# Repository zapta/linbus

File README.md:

ARDUINO LINBUS GADGETS
======================

An Arduino based LINBUS stack that allow to explore and hack linbus based system.

Unless specified otherwise, the PCBs can be used with standard Aruduino IDE, behaving as Arduino Pro Mini 5V 16Mhz with ATMEGA328.

<br>
**Analyzer** - a small PCB that connects on one hand to linbus and to a computer USB port on the other. The analyzer decode all the linbus frames and dump them to the computer. The USB connection emulates a serial port using a builtin FTDI adapter and can be read with standard serial application. A special python script is provided in the tools directory to dump the serial data in diff mode such that only changed bits are displayed. The board design support also linbus TX which allow to have this board functioning as a linbus master or slave (this however requires firmware changes).

<br>
**Beeper** - a small PCB and firmware that monitors a linbus and activates a buzzer when certain conditions met. The provided firmware includes a car specific example that beeps when the reverse gear in my car is engaged. The car specific logic is in the car_module* files and can be adapted to different applications.

<br>
**Injector** - a small PCB board with two linbus interfaces that connects in series between a linbus master and a linbus slave. The injector looks as a slave to the master and as a master to slave and it transparantly proxying LIN frame between the. At the same time, it can monitor bus signals, apply application spefici logic and can inject signals back to the bus by modifying on the fly LIN frames it proxys between the master and the slave. The Injector was developed to modiy the behavior of existing LIN bus based system (e.g. automatic activation of the Sport mode in my car).

<br>
**Feature Comparison**

| Feature | Analyzer | Beeper | Injector |
|----|----|----|----|
| Max LIN speed | 20kps | 20kps | 20kps |
| Min LIN speed | 1kps | 1kps | 1kps |
| Operating voltage | 12V | 12V | 12V |
| Max voltage | 40V | 40V | 40V |
| LIN frame dump/log | Yes | Yes | Yes |
| LIN checksums | V1/V2 | V1/V2 | V1/V2 |
| Computer serial interface | FTDI/USB | Serial 5V | Serial 5V |
| Computer serial speed | 115,200 | 115,200 | 115,200 |
| Audible output | No | Yes | No |
| LIN signal interception | Yes | Yes | Yes |
| LIN signal injection | No | No | Yes |
| Arduino IDE compatible | Yes | Yes | Yes |
| Programming language | C/C++ | C/C++ | C/C++ |
| MCU | ATMEGA328P | ATMEGA328P  | ATMEGA328P |
| MCU speed | 16Mhz | 16Mhz  | 16Mhz |
| Schematic/Layout software | Cadsoft Eagle | Cadsoft Eagle | Cadsoft Eagle |
| PCB Size (inches) | 1.3 x 1.5 | 1.15 x 1.6 | 1.31 x 1.44 |
| PCB layers | 2 | 2 | 2 |
| Component mounting | SMD | SMD | SMD |
| Min component size | 0805 | 0805 | 0805 |
| OSHPark compatible | Yes | Yes | Yes |

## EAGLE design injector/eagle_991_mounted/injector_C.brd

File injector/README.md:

Arduino LINBUS Signal Injector
==============================

The Arduino Linbus injector is a small Arduino based board that connects on a LIN bus between the master and a slave
and can observe and manipulate the data flowing on the bus. It also has a 115kbs serial interface  programming and for logging bus activity on a standard computer (a serial to FTDI USB adapter such as Sparkfun FTDI Basic is required).

The board has two LIN bus ports, one that acts as a slave and should be connected to the LIN bus master and another
 that acts as a master and should be connected to the LIN bus slace. The firmware here includes a set of files named
with the prefix custom_ that implement an application specific logic (simulating pressing the Sport Mode button of my
car whenever the ignition is turned) and should be modified to match the target logic and behavior.

The USB/Serial port is also compatible with the Arduino IDE (emulating an Arduino Mini Pro 16Mhz 5V with Atmega328p) which can be used to edit/compile/download software updates. 

The serial output of the injector can be viewed directly with a terminal emulation software or using the provided script that adds timestamp and bit by bit diff capabilities (see the [serial tool](../tools/serial)).

The injector provided sample application is configured for 19,200bps linbus that uses LIN V2 checksum but be configured 
for busses with different speeds and checksum formula.

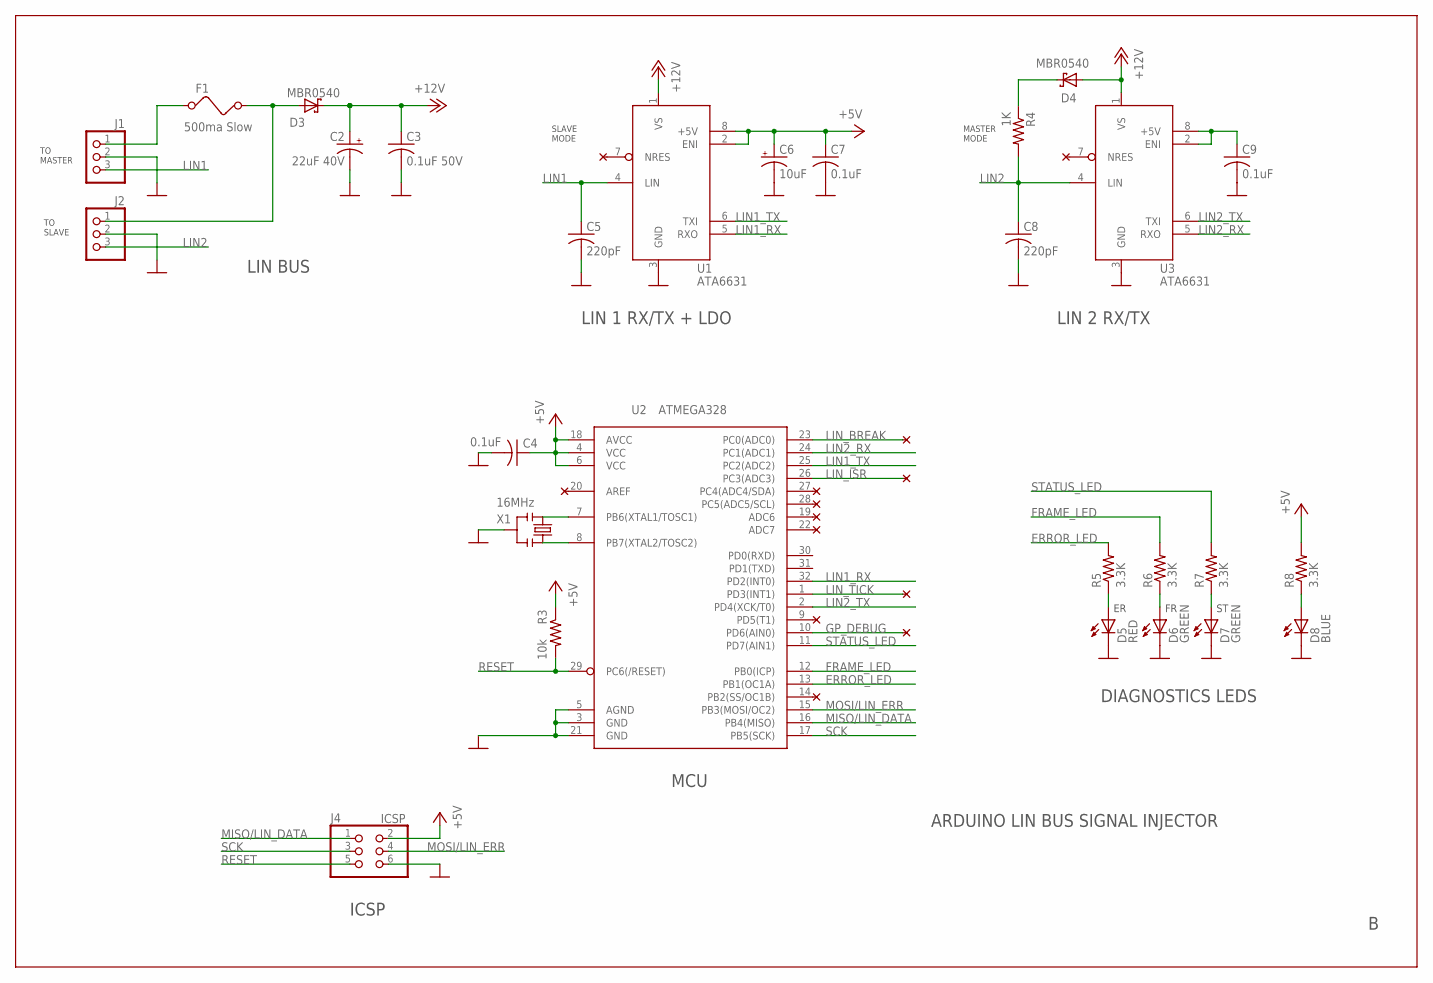
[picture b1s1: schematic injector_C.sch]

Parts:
C2: 22uF 40V; UD-6,3X5,8_NICHICON
C3: 0.1uF 50V; C0805
C4, C7, C9: 0.1uF; C0805
C5, C8: 220pF; C0805
C6: 10uF; A/3216-18R
D3, D4: MBR0540; SOD123FL
D5: RED; 1206-LED
D6, D7: GREEN; 1206-LED
D8: BLUE; 1206-LED
F1: 500ma Slow; 1206
J1, J2: PINHD-1X3; 1X03
J4: ICSP; 2X03
R3: 10k; 1206
R4: 1K; R0805
R5, R6, R7, R8: 3.3K; R0805
U1, U3: ATA6631; SO-08
U2: ATMEGA328; TQFP32-08
X1: 16MHz; RESONATOR-SMD

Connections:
+5V: C4.1, C6.+, C7.1, J4.2, R3.1, R8.2, U1.2 (ENI), U1.8 (+5V), U2.4 (VCC), U2.6 (VCC), U2.18 (AVCC)
+12V: C2.+, C3.1, D3.C, D4.A, U1.1 (VS), U3.1 (VS)
ERROR_LED: R5.2, U2.13 (PB1(OC1A))
FRAME_LED: R6.2, U2.12 (PB0(ICP))
GND: C2.-, C3.2, C4.2, C5.2, C6.-, C7.2, C8.2, C9.2, D5.C, D6.C, D7.C, D8.C, J1.2, J2.2, J4.6, U1.3 (GND), U2.3 (GND), U2.5 (AGND), U2.21 (GND), U3.3 (GND), X1.2
GP_DEBUG: U2.10 (PD6(AIN0))
LIN1: C5.1, J1.3, U1.4 (LIN)
LIN1_RX: U1.5 (RXO), U2.32 (PD2(INT0))
LIN1_TX: U1.6 (TXI), U2.25 (PC2(ADC2))
LIN2: C8.1, J2.3, R4.2, U3.4 (LIN)
LIN2_RX: U2.24 (PC1(ADC1)), U3.5 (RXO)
LIN2_TX: U2.2 (PD4(XCK/T0)), U3.6 (TXI)
LIN_BREAK: U2.23 (PC0(ADC0))
LIN_ISR: U2.26 (PC3(ADC3))
LIN_TICK: U2.1 (PD3(INT1))
MISO/LIN_DATA: J4.1, U2.16 (PB4(MISO))
MOSI/LIN_ERR: J4.4, U2.15 (PB3(MOSI/OC2))
unnamed: D7.A, R7.1
unnamed: D8.A, R8.1
unnamed: D6.A, R6.1
unnamed: D5.A, R5.1
unnamed: D3.A, F1.2, J2.1
unnamed: D4.C, R4.1
RESET: J4.5, R3.2, U2.29 (PC6(/RESET))
SCK: J4.3, U2.17 (PB5(SCK))
SECONDARY_5V: C9.1, U3.2 (ENI), U3.8 (+5V)
STATUS_LED: R7.2, U2.11 (PD7(AIN1))
VBAT: F1.1, J1.1
XTAL1: U2.7 (PB6(XTAL1/TOSC1)), X1.3
XTAL2: U2.8 (PB7(XTAL2/TOSC2)), X1.1

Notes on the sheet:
LIN BUS
DIAGNOSTICS LEDS
ICSP
LIN 1 RX/TX + LDO
LIN 2 RX/TX
MCU
ARDUINO LIN BUS SIGNAL INJECTOR
MASTER MODE
TO MASTER
TO SLAVE
SLAVE MODE

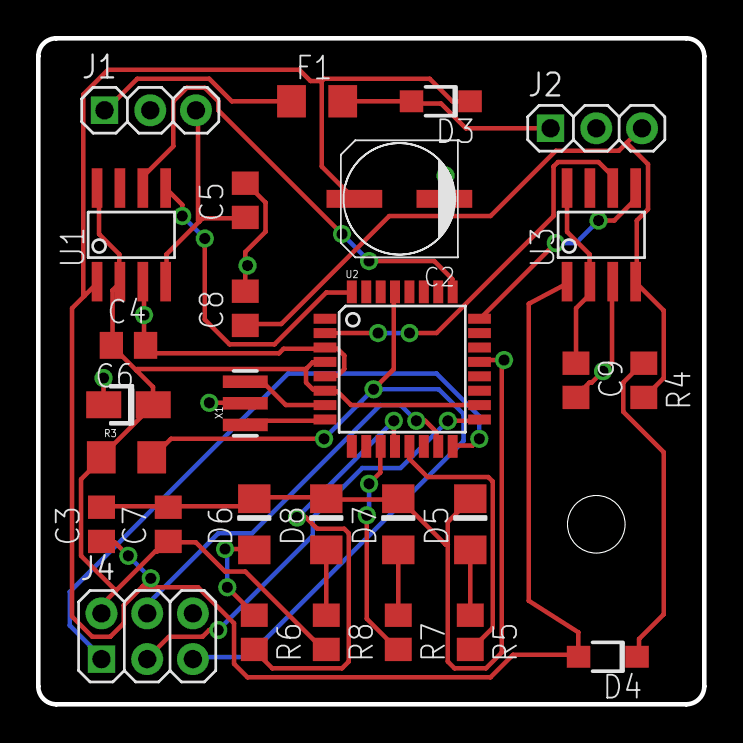
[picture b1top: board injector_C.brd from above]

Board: 2 copper layers, 37.0 x 37.0 mm, 28 parts (0 on the bottom side), 26 nets.

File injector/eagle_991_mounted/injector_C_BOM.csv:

"Part";"Value";"Device";"Package";"Description";"";
"C2";"22uF 40V";"CPOL-USUD-6,3X5,8";"UD-6,3X5,8_NICHICON";"";"";
"C3";"0.1uF 50V";"C-USC0805";"C0805";"";"";
"C4";"0.1uF";"C-USC0805";"C0805";"";"";
"C5";"220pF";"C-USC0805";"C0805";"";"";
"C6";"10uF";"CPOL-USA/3216-18R";"A/3216-18R";"";"";
"C7";"0.1uF";"C-USC0805";"C0805";"";"";
"C8";"220pF";"C-USC0805";"C0805";"";"";
"C9";"0.1uF";"C-USC0805";"C0805";"";"";
"D3";"MBR0540";"SMF5.0AT1";"SOD123FL";"";"";
"D4";"MBR0540";"SMF5.0AT1";"SOD123FL";"";"";
"D5";"RED";"LED";"1206-LED";"";"";
"D6";"GREEN";"LED";"1206-LED";"";"";
"D7";"GREEN";"LED";"1206-LED";"";"";
"D8";"BLUE";"LED";"1206-LED";"";"";
"F1";"500ma Slow";"FUSE";"1206";"";"";
"J1";"";"PINHD-1X3";"1X03";"";"";
"J2";"";"PINHD-1X3";"1X03";"";"";
"J4";"ICSP";"PINHD-2X3";"2X03";"";"";
"R3";"10k";"RESISTOR1206";"1206";"Resistor";"";
"R4";"1K";"R-US_R0805";"R0805";"";"";
"R5";"3.3K";"R-US_R0805";"R0805";"";"";
"R6";"3.3K";"R-US_R0805";"R0805";"";"";
"R7";"3.3K";"R-US_R0805";"R0805";"";"";
"R8";"3.3K";"R-US_R0805";"R0805";"";"";
"U1";"ATA6631";"ATA6631";"SO-08";"";"";
"U2";"ATMEGA328";"ATMEGA328";"TQFP32-08";"";"";
"U3";"ATA6631";"ATA6631";"SO-08";"";"";
"X1";"16MHz";"RESONATORSMD";"RESONATOR-SMD";"";"";

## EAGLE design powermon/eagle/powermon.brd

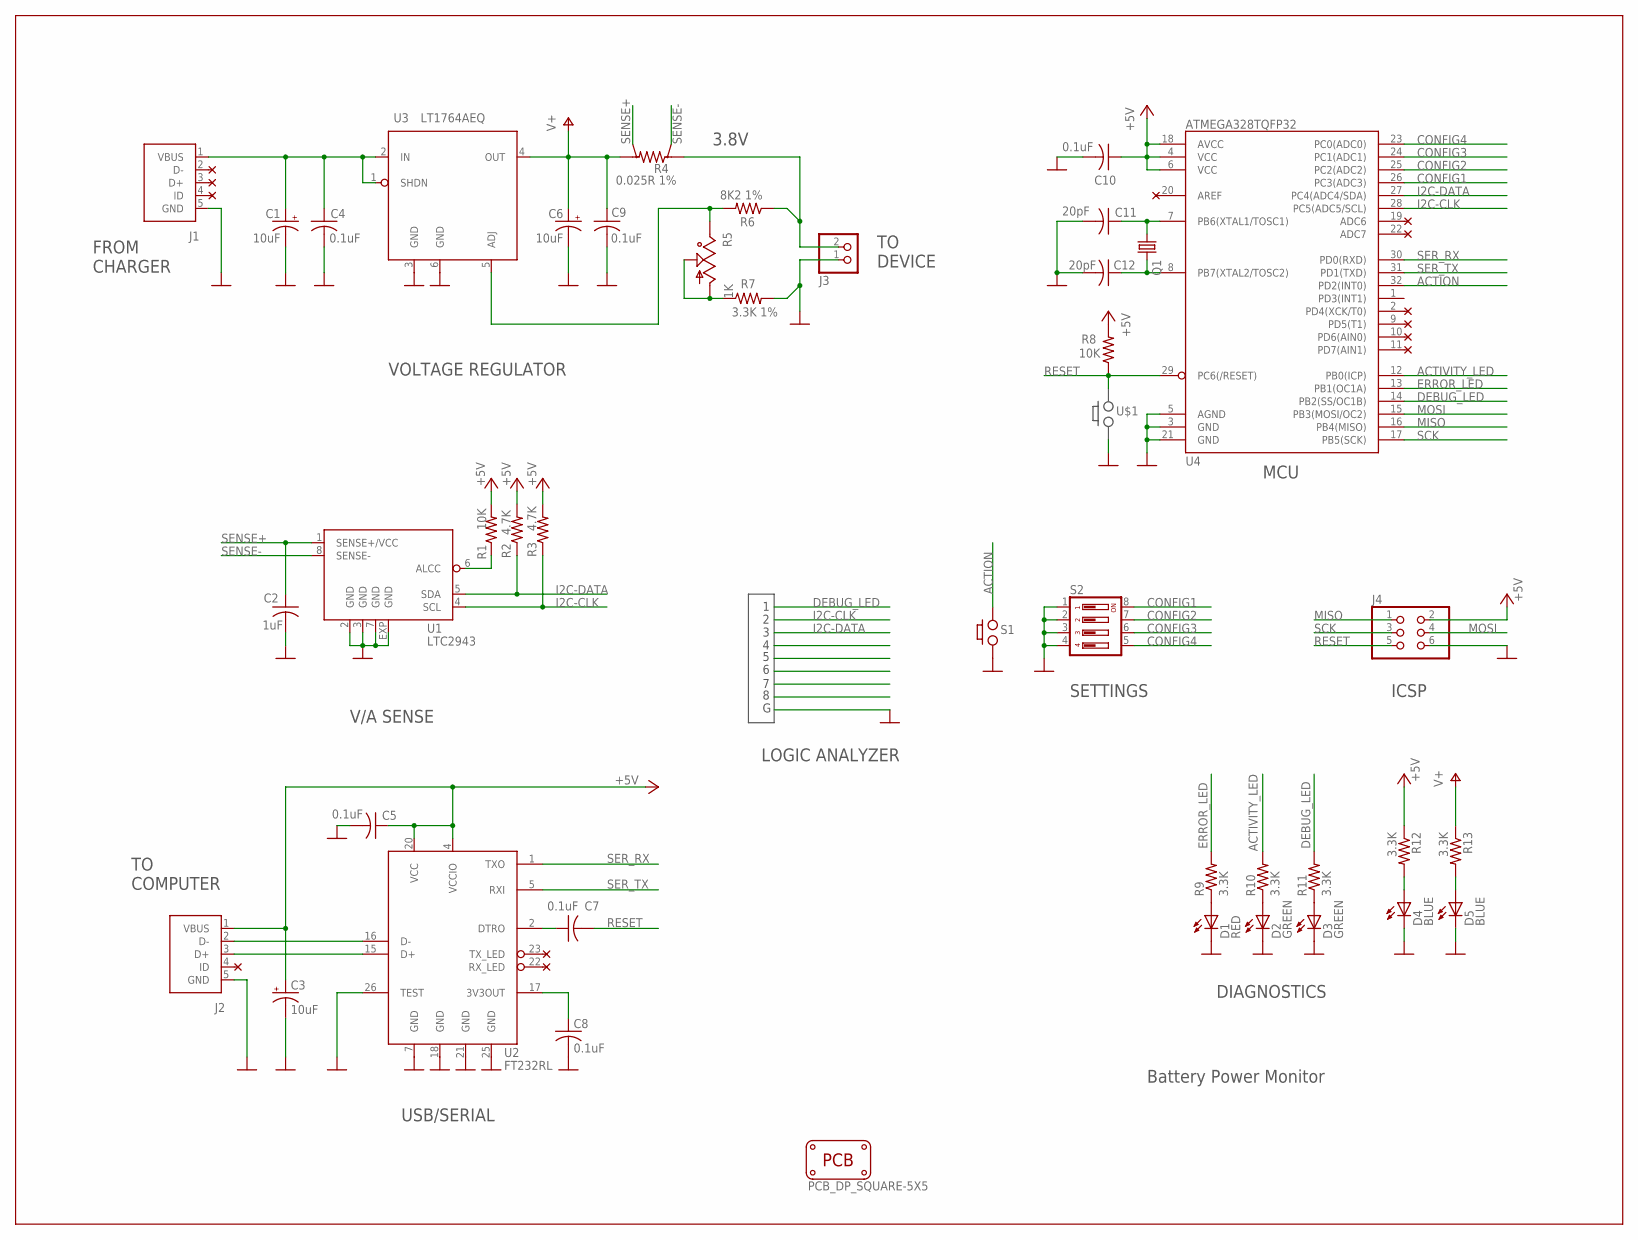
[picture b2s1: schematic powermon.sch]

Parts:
C1, C3, C6: 10uF; A/3216-18R
C2: 1uF; C0603
C4, C5, C7, C8, C9, C10: 0.1uF; C0603
C11, C12: 20pF; C0603
D1: RED; 1206-LED
D2, D3: GREEN; 1206-LED
D4, D5: BLUE; 1206-LED
J1, J2: USB; USB-MICRO-ZX62RD-AB-5P8
J3: TERMINAL-2
J4: PINHD-2X3; 2X03
PCB1: PCB_DP_SQUARE-5X5; DP5050_V1
Q1: CRYSTALCTS406; CRYSTAL-CTS406
R1, R8: 10K; R0603
R2, R3: 4.7K; R0603
R4: 0.025R 1%; SHUNT
R5: 1K; TRIM-POT_SM-42/43A
R6: 8K2 1%; R0603
R7: 3.3K 1%; R0603
R9, R10, R11, R12, R13: 3.3K; R0603
S1: PUSH_BUTTONEVQPSL; EVQPSL-PUSH-BUTTON
S2: 219-04; CTS-219-04
U1: LTC2943; DFN8-3X3
U2: FT232RL; SSOP28DB
U3: LT1764AEQ; TO263-5
U4: ATMEGA328TQFP32; TQFP32-08

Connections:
+5V: C3.+, C5.1, C10.1, J2.1 (VBUS), J4.2, R1.2, R2.2, R3.2, R8.2, R12.1, U2.4 (VCCIO), U2.20 (VCC), U4.4 (VCC), U4.6 (VCC), U4.18 (AVCC)
ACTION: S1.1 (2), U4.32 (PD2(INT0))
ACTIVITY_LED: R10.2, U4.12 (PB0(ICP))
CONFIG1: S2.8, U4.26 (PC3(ADC3))
CONFIG2: S2.7, U4.25 (PC2(ADC2))
CONFIG3: S2.6, U4.24 (PC1(ADC1))
CONFIG4: S2.5, U4.23 (PC0(ADC0))
DEBUG_LED: R11.2, U4.14 (PB2(SS/OC1B))
ERROR_LED: R9.2, U4.13 (PB1(OC1A))
GND: C1.-, C2.2, C3.-, C4.2, C5.2, C6.-, C8.2, C9.2, C10.2, C11.2, C12.2, D1.C, D2.C, D3.C, D4.C, D5.C, J1.5 (GND), J2.5 (GND), J3.1, J4.6, R7.2, S1.2 (1), S2.1, S2.2, S2.3, S2.4, U1.2 (GND), U1.3 (GND), U1.7 (GND), U1.EXP (GND), U2.7 (GND), U2.18 (GND), U2.21 (GND), U2.25 (GND), U2.26 (TEST), U3.3 (GND), U3.6 (GND), U4.3 (GND), U4.5 (AGND), U4.21 (GND)
I2C-CLK: R3.1, U1.4 (SCL), U4.28 (PC5(ADC5/SCL))
I2C-DATA: R2.1, U1.5 (SDA), U4.27 (PC4(ADC4/SDA))
MISO: J4.1, U4.16 (PB4(MISO))
MOSI: J4.4, U4.15 (PB3(MOSI/OC2))
unnamed: R1.1, U1.6 (ALCC)
unnamed: C11.1, Q1.1, U4.7 (PB6(XTAL1/TOSC1))
unnamed: D2.A, R10.1
unnamed: D1.A, R9.1
unnamed: C12.1, Q1.3 (2), U4.8 (PB7(XTAL2/TOSC2))
unnamed: C1.+, C4.1, J1.1 (VBUS), U3.1 (SHDN), U3.2 (IN)
unnamed: J2.3 (D+), U2.15 (D+)
unnamed: C7.1, U2.2 (DTRO)
unnamed: D5.A, R13.2
unnamed: J2.2 (D-), U2.16 (D-)
unnamed: C8.1, U2.17 (3V3OUT)
unnamed: D4.A, R12.2
unnamed: R5.1, R5.2, R7.1
unnamed: R5.3, R6.2, U3.5 (ADJ)
unnamed: D3.A, R11.1
unnamed: J3.2, R4.I1, R6.1
RESET: C7.2, J4.5, R8.1, U4.29 (PC6(/RESET))
SCK: J4.3, U4.17 (PB5(SCK))
SENSE+: C2.1, R4.V2, U1.1 (SENSE+/VCC)
SENSE-: R4.V1, U1.8 (SENSE-)
SER_RX: U2.1 (TXO), U4.30 (PD0(RXD))
SER_TX: U2.5 (RXI), U4.31 (PD1(TXD))
V+: C6.+, C9.1, R4.I2, R13.1, U3.4 (OUT)

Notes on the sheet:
USB/SERIAL
ICSP
MCU
Battery Power Monitor
DIAGNOSTICS
V/A SENSE
VOLTAGE REGULATOR
FROM CHARGER
LOGIC ANALYZER
TO COMPUTER
TO DEVICE
SETTINGS
3.8V

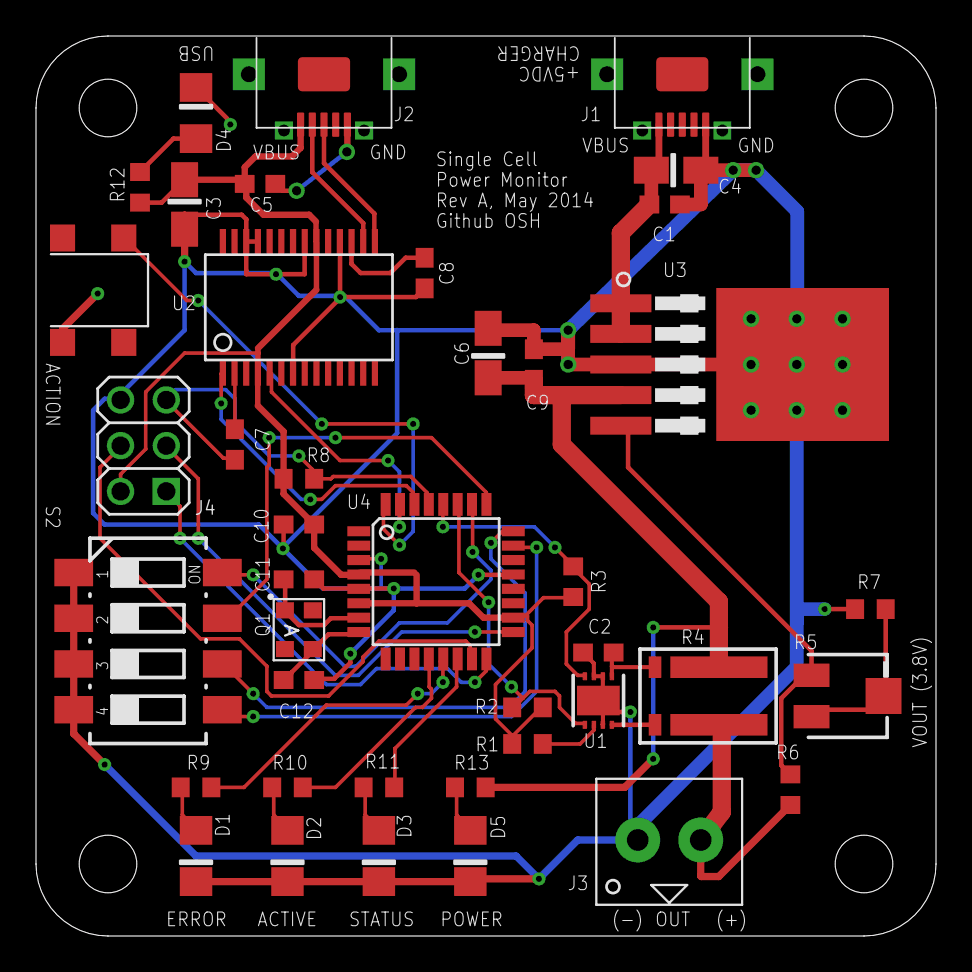
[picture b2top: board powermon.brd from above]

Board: 2 copper layers, 50.0 x 50.0 mm, 42 parts (0 on the bottom side), 37 nets.

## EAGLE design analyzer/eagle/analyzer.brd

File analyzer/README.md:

Arduino LINBUS Analyzer
=======================

The Arduino Linbus analyzer is a small Arduino based board that connects to a LIN bus on one end and to a computer USB port on the other. The Analyzer decods the frames on the LIN bus and send them to the computer as human readable text over virtual serial port (115.2kbs, 8 data bit, 1 start bit, 1 stop bit, no parity).

The board has two 3 pin LIN bus parallel connections such that one can be connected to the master and the other to the slave. The USB/Serial port is FTDI based and should be compatible with Mac OSX, Linux and Windows.

The USB/Serial port is also compatible with the Arduino IDE (emulating an Arduino Mini Pro 16Mhz 5V with Atmega328p) which can be used to edit/compile/download software updates. 

The output of the analyzer can be viewed directly with a terminal emulation software or using the provided script that ads timestamp and bit by bit diff capabilities (see .

The analyzer is hard coded to decode buss signals at 19,200bps and LIN bus enhanced checksum (V2). This can change in the source code (use the Arduino IDE) and downloaded to the Analyzer.

**Connectors**

J1 - LIN bus connection to the master.

J2 - LIN bus connection to the slave (connected 1:1 to J1)

J3 - FTDI Serial over USB connection to the computer.

J4 - Master mode jumper. Not used. Leave opened.

J5 - ICSP port. Used for one time programming of the Arduino bootloader in production.

**LED indicators**

D5 - Errors LED. Blinks when the analyzer detects LIN bus errors.

D6 - Frame LED, blinks when valid LIN bus frames are detected. Also blinks slow in idle state to indicates that the board is alive.

D7 - Power indicator. On when the board is powered, from the LIN bus or from the USB port.

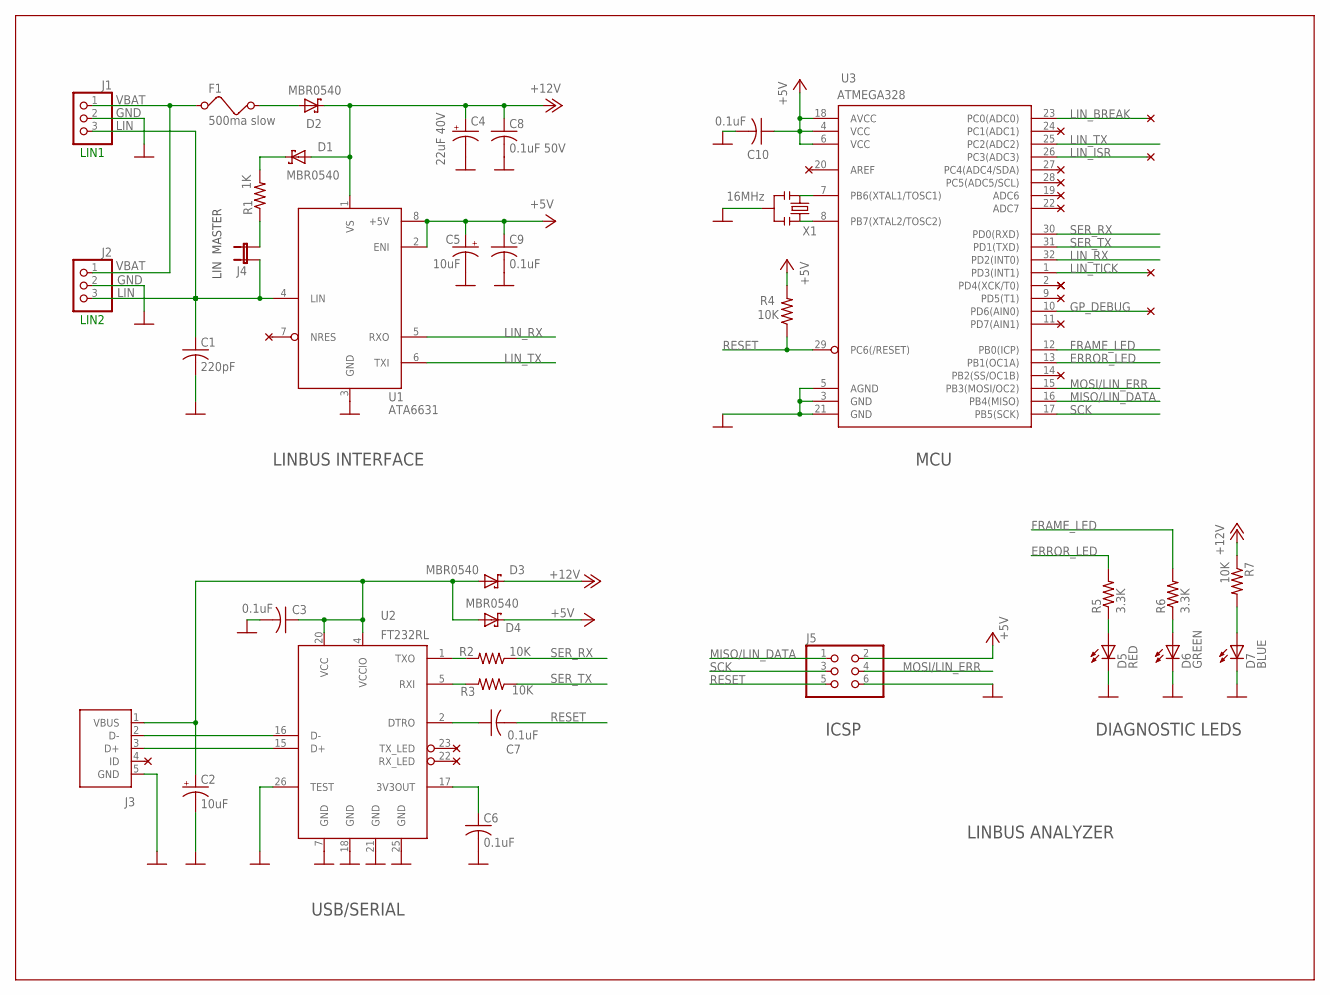
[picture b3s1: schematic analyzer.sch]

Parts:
C1: 220pF; C0805
C2, C5: 10uF; A/3216-18R
C3, C6, C7, C9, C10: 0.1uF; C0805
C4: 22uF 40V; UD-6,3X5,8_NICHICON
C8: 0.1uF 50V; C0805
D1, D2, D3, D4: MBR0540; SOD123FL
D5: RED; 1206-LED
D6: GREEN; 1206-LED
D7: BLUE; 1206-LED
F1: 500ma slow; 1206
J1, J2: PINHD-1X3; 1X03
J3: USBSMD; USB-MINIB
J4: JP1E; JP1
J5: PINHD-2X3; 2X03
R1: 1K; R0805
R2, R3, R4, R7: 10K; R0805
R5, R6: 3.3K; R0805
U1: ATA6631; SO-08
U2: FT232RL; SSOP28DB
U3: ATMEGA328; TQFP32-08
X1: 16MHz; RESONATOR-SMD

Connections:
+5V: C5.+, C9.1, C10.1, D4.C, J5.2, R4.2, U1.2 (ENI), U1.8 (+5V), U3.4 (VCC), U3.6 (VCC), U3.18 (AVCC)
+12V: C4.+, C8.1, D1.A, D2.C, D3.C, R7.1, U1.1 (VS)
ERROR_LED: R5.2, U3.13 (PB1(OC1A))
FRAME_LED: R6.2, U3.12 (PB0(ICP))
GND: C1.2, C2.-, C3.2, C4.-, C5.-, C6.2, C8.2, C9.2, C10.2, D5.C, D6.C, D7.C, J1.2, J2.2, J3.5 (GND), J5.6, U1.3 (GND), U2.7 (GND), U2.18 (GND), U2.21 (GND), U2.25 (GND), U2.26 (TEST), U3.3 (GND), U3.5 (AGND), U3.21 (GND), X1.2
GP_DEBUG: U3.10 (PD6(AIN0))
LIN: C1.1, J1.3, J2.3, J4.1, U1.4 (LIN)
LIN_BREAK: U3.23 (PC0(ADC0))
LIN_ISR: U3.26 (PC3(ADC3))
LIN_RX: U1.5 (RXO), U3.32 (PD2(INT0))
LIN_TICK: U3.1 (PD3(INT1))
LIN_TX: U1.6 (TXI), U3.25 (PC2(ADC2))
MISO/LIN_DATA: J5.1, U3.16 (PB4(MISO))
MOSI/LIN_ERR: J5.4, U3.15 (PB3(MOSI/OC2))
unnamed: U3.8 (PB7(XTAL2/TOSC2)), X1.1
unnamed: D6.A, R6.1
unnamed: D5.A, R5.1
unnamed: R3.2, U2.5 (RXI)
unnamed: D2.A, F1.2
unnamed: U3.7 (PB6(XTAL1/TOSC1)), X1.3
unnamed: D1.C, R1.2
unnamed: J4.2, R1.1
unnamed: J3.3 (D+), U2.15 (D+)
unnamed: C7.1, U2.2 (DTRO)
unnamed: C2.+, C3.1, D3.A, D4.A, J3.1 (VBUS), U2.4 (VCCIO), U2.20 (VCC)
unnamed: R2.2, U2.1 (TXO)
unnamed: J3.2 (D-), U2.16 (D-)
unnamed: C6.1, U2.17 (3V3OUT)
unnamed: D7.A, R7.2
RESET: C7.2, J5.5, R4.1, U3.29 (PC6(/RESET))
SCK: J5.3, U3.17 (PB5(SCK))
SER_RX: R2.1, U3.30 (PD0(RXD))
SER_TX: R3.1, U3.31 (PD1(TXD))
VBAT: F1.1, J1.1, J2.1

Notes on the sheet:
LIN1
LIN2
USB/SERIAL
LINBUS INTERFACE
ICSP
MCU
LINBUS ANALYZER
DIAGNOSTIC LEDS
LIN MASTER

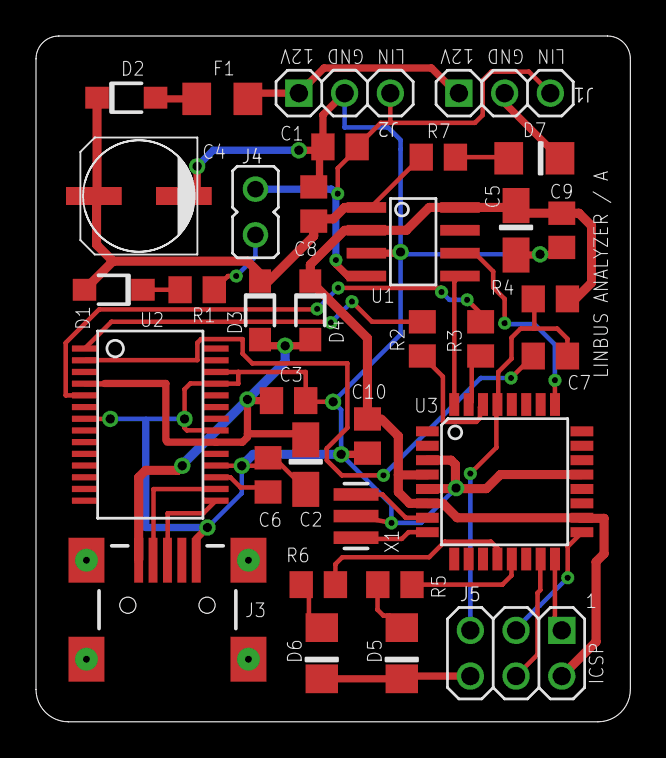
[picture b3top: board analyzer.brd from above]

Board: 2 copper layers, 33.0 x 38.1 mm, 34 parts (0 on the bottom side), 30 nets.

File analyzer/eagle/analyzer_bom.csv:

"QTY","PARTS","VALUE","Package","SAMPLE SOURCE","COMMENTS"
"1","C1","Ceramic capacitor 220pF 50V","0805","Digikey 311-1123-1-ND",
"2","C2, C5","Tantalum Capacitor 10uF, 10V","1206","Digikey 399-3684-1-ND",
"6","C3, C6, C7, C8, C9, C10","Capacitor 0.1uF ceramic, 50V","0805","Digikey 399-1179-1-ND",
"1","C4","Aluminum capacitor 22uF 20% 40V","4mm x 5.8mm","Digikey 493-2300-1-ND",
"4","D1, D2, D3, D4","MBR0540","SOD-123","Digikey MBR0540TPMSCT-ND",
"1","D5","Red LED","1206","Sparkfun PRT-12619","High brightness, operate at ~1ma."
"1","D6","Green LED","1206","Sparkfun PRT-12622","High brightness, operate at ~1ma."
"1","D7","Red Blue","1206","Sparkfun PRT-12620","High brightness, operate at ~1ma."
"1","F1","Fuse, 500ma Slow","1206","Digikey SF-1206S050-2CT-ND","Must be slow, otherwise will blow on startup."
"2","J1, J2","0.1"" 1x3 right angle header.",,"Digikey WM50026-03-ND",
"1","J3","USB Min B SMD connector",,"Digikey 609-4701-1-ND","With two guide pins."
"1","J4","0.1"" 1x2 header.",,"Digikey 952-2261-ND",
"1","J5","0.1"" 2*3 header",,"Digikey 952-2120-ND",
"1","R1","Resistor 1K 1/8W 5%","0805","Dgikey RMCF0805JT1K00CT-ND",
"4","R2, R3, R4,R7","Resistor 10k 1/8W 5%","0805","Digikey RMCF0805JT10K0CT-ND",
"2","R5, R6","Resistor 3.3K 1/8W 5%","0805","Digikey RMCF0805JT3K30CT-ND",
"1","U1","ATA6631 LINBUS + LDO","SO-08","Digikey ATA6663-TAQYCT-ND",
"1","U2","FT232RL USB/Serial","SSOP28DB","Digikey 768-1007-1-ND",
"1","U3","ATMEGA328P  AVR MCU","TQFP32-08","Digikey ATMEGA328P-15AZTR-ND",
"1","X1","Resonator 16MHz with internal capacitors","1.3mm x 3.2mm","Digikey 490-1198-1-ND",
"1","PCB","Linbus Analyzer PCB Rev A",,"https://oshpark.com/shared_projects/YeGPKyFt","2 Layers board. OSHPARK charges a total of about $10 for a set of three."

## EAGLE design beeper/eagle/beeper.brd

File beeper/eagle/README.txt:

Feb 2014.

The Linbus Beeeper board was design to have only two layers and
comply with design rules of inexpensive PCB houses. The components
sizes were selected to be large enough for manual soldering by 
hobbyist (e.g. 805 SMD resistors). 

Most PCB houses accept Eagle files so to order you just need to
upload the Eagle file, without having to generate gerber files.

For example, in the US oshpark.com will manufacture 3 boards for
a total of $10 including shipping (as of Jan 2014).

If you are ordering from ospark.com, you may find the board already
ready for ordering at http://oshpark.com/profiles/zapta (there is
no special deal or commission when ordering via this link, just
saving you the need to upload the file).

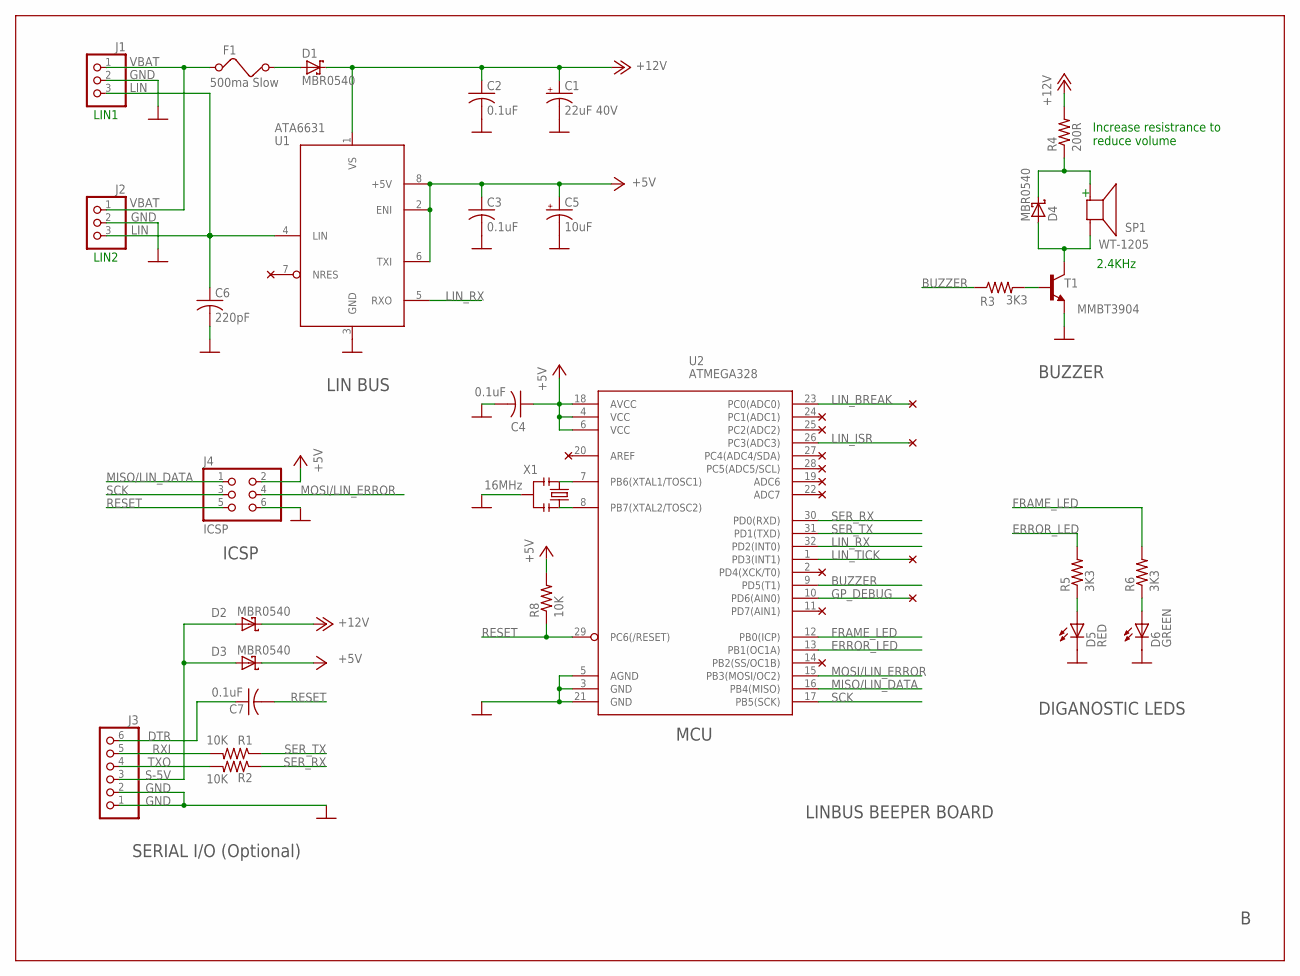
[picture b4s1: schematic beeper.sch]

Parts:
C1: 22uF 40V; UD-6,3X5,8_NICHICON
C2, C3, C4, C7: 0.1uF; C0805
C5: 10uF; A/3216-18R
C6: 220pF; C0805
D1, D2, D3, D4: MBR0540; SOD123FL
D5: RED; 1206-LED
D6: GREEN; 1206-LED
F1: 500ma Slow; 1206
J1, J2: PINHD-1X3; 1X03
J3: PINHD-1X6; 1X06
J4: ICSP; 2X03
R1, R2, R8: 10K; R0805
R3, R5, R6: 3K3; R0805
R4: 200R; R0805
SP1: WT-1205; AL60P
T1: MMBT3904; SOT23-BEC
U1: ATA6631; SO-08
U2: ATMEGA328; TQFP32-08
X1: 16MHz; RESONATOR-SMD

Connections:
+5V: C3.1, C4.1, C5.+, D3.C, J4.2, R8.2, U1.2 (ENI), U1.6 (TXI), U1.8 (+5V), U2.4 (VCC), U2.6 (VCC), U2.18 (AVCC)
+12V: C1.+, C2.1, D1.C, D2.C, R4.2, U1.1 (VS)
BUZZER: R3.1, U2.9 (PD5(T1))
DTR: C7.1, J3.6
ERROR_LED: R5.2, U2.13 (PB1(OC1A))
FRAME_LED: R6.2, U2.12 (PB0(ICP))
GND: C1.-, C2.2, C3.2, C4.2, C5.-, C6.2, D5.C, D6.C, J1.2, J2.2, J3.1, J3.2, J4.6, T1.E, U1.3 (GND), U2.3 (GND), U2.5 (AGND), U2.21 (GND), X1.2
GP_DEBUG: U2.10 (PD6(AIN0))
LIN: C6.1, J1.3, J2.3, U1.4 (LIN)
LIN_BREAK: U2.23 (PC0(ADC0))
LIN_ISR: U2.26 (PC3(ADC3))
LIN_RX: U1.5 (RXO), U2.32 (PD2(INT0))
LIN_TICK: U2.1 (PD3(INT1))
MISO/LIN_DATA: J4.1, U2.16 (PB4(MISO))
MOSI/LIN_ERROR: J4.4, U2.15 (PB3(MOSI/OC2))
unnamed: D6.A, R6.1
unnamed: D5.A, R5.1
unnamed: D1.A, F1.2
unnamed: R3.2, T1.B
unnamed: D4.C, R4.1, SP1.1
unnamed: D4.A, SP1.2, T1.C
RESET: C7.2, J4.5, R8.1, U2.29 (PC6(/RESET))
RXI: J3.5, R1.2
S-5V: D2.A, D3.A, J3.3
SCK: J4.3, U2.17 (PB5(SCK))
SER_RX: R2.1, U2.30 (PD0(RXD))
SER_TX: R1.1, U2.31 (PD1(TXD))
TXO: J3.4, R2.2
VBAT: F1.1, J1.1, J2.1
XTAL1: U2.7 (PB6(XTAL1/TOSC1)), X1.3
XTAL2: U2.8 (PB7(XTAL2/TOSC2)), X1.1

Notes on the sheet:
LIN1
LIN2
2.4KHz
LIN BUS
ICSP
SERIAL I/O (Optional)
MCU
DIGANOSTIC LEDS
BUZZER
Increase resistrance to reduce volume
LINBUS BEEPER BOARD

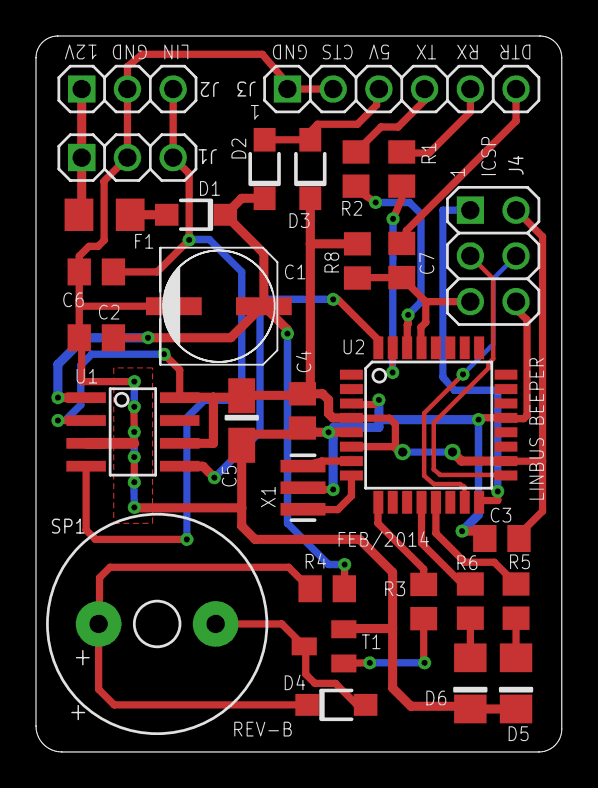
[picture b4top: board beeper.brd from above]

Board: 2 copper layers, 29.2 x 39.8 mm, 30 parts (0 on the bottom side), 27 nets.

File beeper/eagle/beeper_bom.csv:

"QTY","PARTS","VALUE","PACKAGE","SAMPLE SOURCE","COMMENTS"
1,"J1","0.1"" 1x3 right angle header.",,"Digikey WM50026-03-ND","The Linbsu connector from the master plugs into to this header (pay attention to polarity)."
1,"J2","3 wire pigtail to a 3 pin  0.1” Servo Connector.",,"http://bit.ly/1eFYfS3",
1,"J3","0.1"" 1x6 header",,"Digikey WM50026-06-ND","For software development only, not needed for normal buzzer operation."
1,"J4","0.1"" 2*3 header",,"Digikey 952-2120-ND","Can be omitted if programming using pogo pins."
1,"F1","Fuse, 500ma Slow","1206","Digikey SF-1206S050-2CT-ND","Do not use a fast fuse, it may blow on power up. A lower 250ma slow fuse should also be fine. If you cannot find a fuse, a 10ohm 1/8w resistor may also work."
1,"C1","Aluminum capacitor 22uF 20% 40V","4mm x 5.8mm","Digikey 493-2300-1-ND","Diameter x Height in mm."
4,"C2, C3, C4,C7","Capacitor 0.1uF ceramic, 50V","0805","Digikey 399-1179-1-ND",
1,"C5","Tantalum Capacitor 10uF, 10V","1206","Digikey 399-3684-1-ND",
1,"C6","Ceramic capacitor 220pF 50V","0805","Digikey 311-1123-1-ND",
3,"R1, R2, R8","Resistor 10k 1/8W 5%","0805","Digikey RMCF0805JT10K0CT-ND",
1,"R4","Resistor 100 ohm 1/8W 5%","0805","Digikey RMCF0805JT100RCT-ND","Change value to increase/decrease beeper volume."
4,"R3, R5, R6, R7","Resistor 3.3K 1/8W 5%","0805","Digikey RMCF0805JT3K30CT-ND",
3,"D1, D2, D3, D4","MBR0540","SOD-123","Digikey MBR0540TPMSCT-ND","Schottky diode 40V 500ma."
1,"D5","Red LED","1206","Sparkfun PRT-12619","Low current high brightness red LED (used at 1ma forward current)."
1,"D6","Green LED","1206","Sparkfun PRT-12622","Low current high brightness green LED (used at 1ma forward current)."
1,"X1","Resonator 16MHz with internal capacitors","1.3mm x 3.2mm","Digikey 490-1198-1-ND",
1,"T1","MMBT3904 NPN transistor","SOT-23","Digikey MMBT3904FSCT-ND","general purpose NPN Transistor"
1,"U1","ATA6631 LINBUS + LDO","SOIC 8","Digikey ATA6663-TAQYCT-ND","Prefer high temperature part."
1,"U2","ATMEGA328P  AVR MCU","TQFP 32","Digikey ATMEGA328P-15AZTR-ND","Prefer high temperature part."
1,"SP1","CEM-1212S 0V-12Vp magnetic buzzer","12mm diameter, 6.5mm spacing.","Digikey 102-1156-ND","12mm electro magnetic buzzer. Operated at 0-12V, 2400Hz."
1,"PCB","LINBUS Beeper PCB Rev B",,"http://oshpark.com/shared_projects/skoN2gf1","OSHPark provides 3 boards for about $10 (as of Feb 2014). alternatively, order from the PCB house of your choice (2 layer)."
1,,"1"" clear heat shrink tube",,"Digikey A100C-4-ND ","Use a short piece to protect the board. Cut a hole for the buzzer sound output. Clear material is require to view the status LEDs."

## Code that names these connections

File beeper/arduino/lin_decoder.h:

// Licensed under the Apache License, Version 2.0 (the "License");
// you may not use this file except in compliance with the License.
// You may obtain a copy of the License at
//
//    http://www.apache.org/licenses/LICENSE-2.0
//
// Unless required by applicable law or agreed to in writing, software
// distributed under the License is distributed on an "AS IS" BASIS,
// WITHOUT WARRANTIES OR CONDITIONS OF ANY KIND, either express or implied.
// See the License for the specific language governing permissions and
// limitations under the License.

#ifndef LIN_DECODER_H
#define LIN_DECODER_H

#include "avr_util.h"
#include "lin_frame.h"

// Uses 
// * Timer2 - used to generate the bit ticks.
// * OC2B (PD3) - timer output ticks. For debugging. If needed, can be changed
//   to not using this pin.
// * PD2 - LIN RX input.
// * PC0, PC1, PC2, PC3 - debugging outputs. See .cpp file for details.
namespace lin_decoder {
  // Call once in program setup. Supported baud range is 1000 to 20000. If
  // out of range, using silently default baud of 9600.
  extern void setup(uint16 baud);

  // Try to read next available rx frame. If available, return true and set
  // given buffer. Otherwise, return false and leave *buffer unmodified. 
  // The sync, id and checksum bytes of the frame as well as the total byte
  // count are not verified. 
  extern boolean readNextFrame(LinFrame* buffer);

  // Errors byte masks for the individual error bits.
  namespace errors {
  static const uint8 FRAME_TOO_SHORT = (1 << 0);
  static const uint8 FRAME_TOO_LONG = (1 << 1);
  static const uint8 START_BIT = (1 << 2);
  static const uint8 STOP_BIT = (1 << 3);
  static const uint8 SYNC_BYTE = (1 << 4);
  static const uint8 BUFFER_OVERRUN = (1 << 5);
  static const uint8 OTHER = (1 << 6);
  }

  // Get current error flag and clear it. 
  extern uint8 getAndClearErrorFlags();
  
  // Print to sio a list of error flags.
  extern void printErrorFlags(uint8 lin_errors);
}

#endif  

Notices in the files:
parts and their libraries:
SparkFun: Licensing: CC v3.0 Share-Alike You are welcome to use this library for commercial purposes.
